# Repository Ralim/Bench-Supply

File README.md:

# Bench-Supply
Small Bench Power Supply files, creating a 48V bench power supply.
This will most likely just contain all the board files used.

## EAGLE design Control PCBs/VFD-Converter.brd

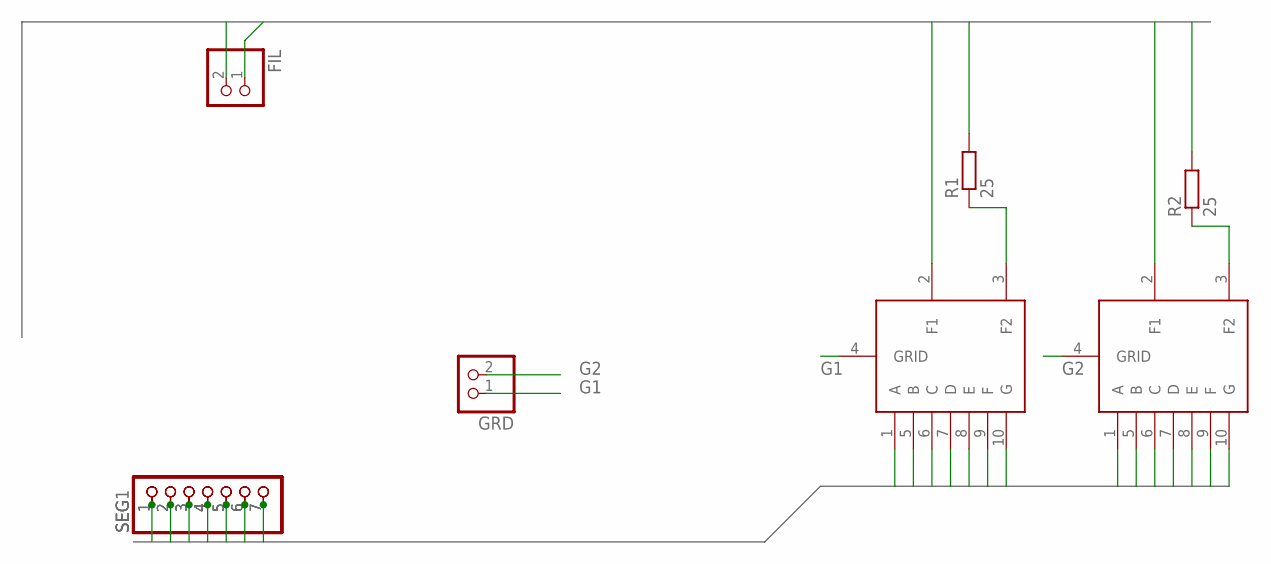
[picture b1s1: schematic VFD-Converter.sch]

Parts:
FIL: PINHD-1X2; 1X02
GRD: PINHD-1X2; 1X02
R1, R2: 25; M0805
SEG, SEG1: PINHD-1X7; 1X07
U$5, U$6: IV-12; NIXIE-11

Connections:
F1: FIL.1, U$5.2 (F1), U$6.2 (F1)
F2: FIL.2, R1.2, R2.2
G1: GRD.1, U$5.4 (GRID)
G2: GRD.2, U$6.4 (GRID)
unnamed: R2.1, U$6.3 (F2)
unnamed: R1.1, U$5.3 (F2)
SEG1: SEG.1, SEG1.1, U$5.1 (A), U$6.1 (A)
SEG2: SEG.2, SEG1.2, U$5.5 (B), U$6.5 (B)
SEG3: SEG.3, SEG1.3, U$5.6 (C), U$6.6 (C)
SEG4: SEG.4, SEG1.4, U$5.7 (D), U$6.7 (D)
SEG5: SEG.5, SEG1.5, U$5.8 (E), U$6.8 (E)
SEG6: SEG.6, SEG1.6, U$5.9 (F), U$6.9 (F)
SEG7: SEG.7, SEG1.7, U$5.10 (G), U$6.10 (G)

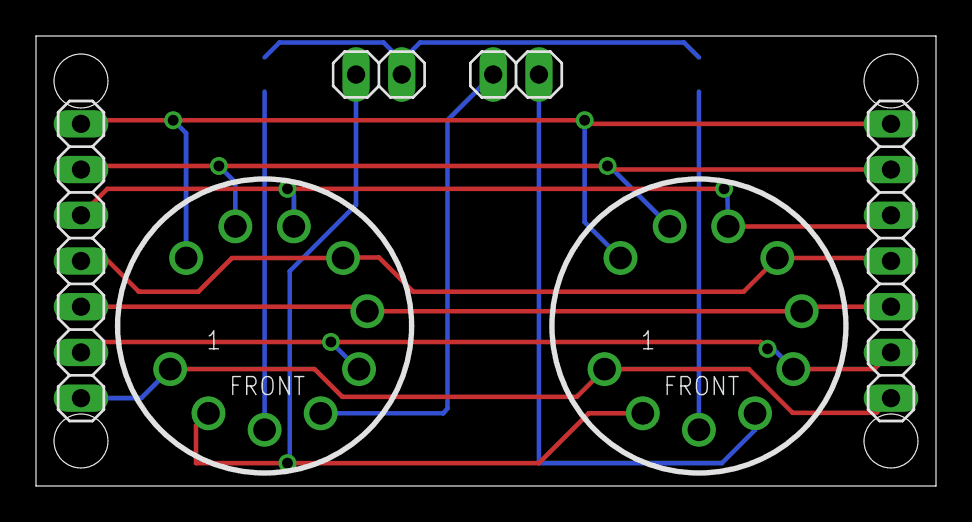
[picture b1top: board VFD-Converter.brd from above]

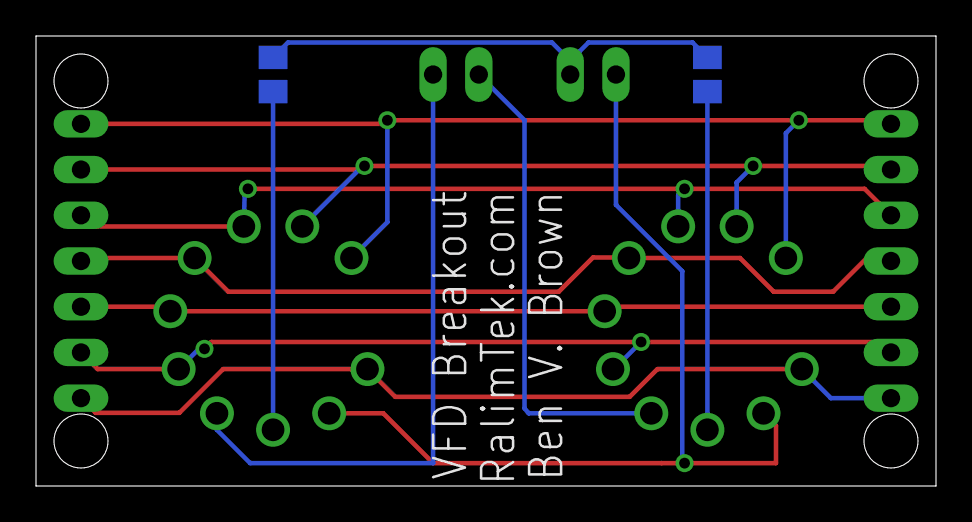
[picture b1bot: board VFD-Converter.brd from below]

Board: 2 copper layers, 50.0 x 25.0 mm, 8 parts (2 on the bottom side), 13 nets.

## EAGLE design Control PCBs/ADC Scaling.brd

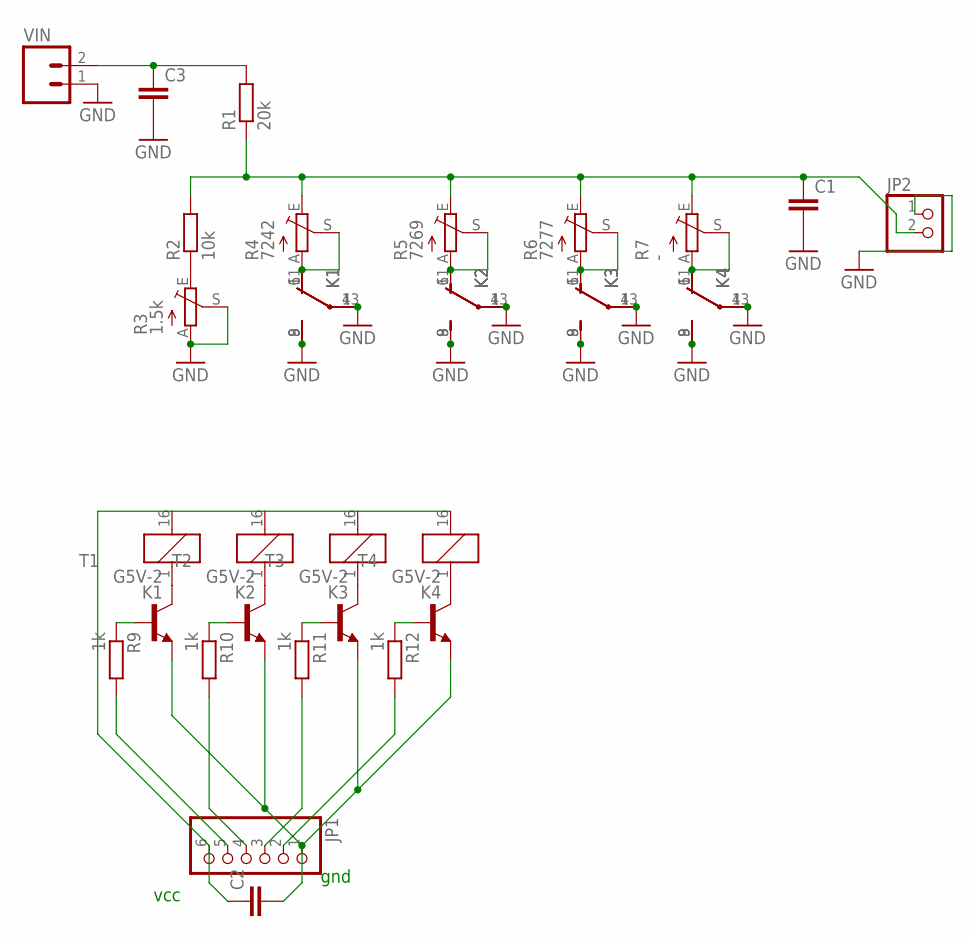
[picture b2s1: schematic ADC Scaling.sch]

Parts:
C1, C2, C3: C-EUC0805; C0805
JP1: PINHD-1X6; 1X06
JP2: PINHD-1X2; 1X02
K1, K2, K3, K4: G5V-2
R1: 20k; M0805
R2: 10k; M0805
R3: 1.5k; RJ9W
R4: 7242; RJ9W
R5: 7269; RJ9W
R6: 7277; RJ9W
R7: -; RJ9W
R9, R10, R11, R12: 1k; M0805
T1, T2, T3, T4: MMBTA42LT1-NPN-SOT23-BEC; SOT23-BEC
VIN: M02POLAR; MOLEX-1X2

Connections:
GND: C1.2, C3.2, JP2.1, K1.4, K1.8 (S), K1.9 (S), K1.13, K2.4, K2.8 (S), K2.9 (S), K2.13, K3.4, K3.8 (S), K3.9 (S), K3.13, K4.4, K4.8 (S), K4.9 (S), K4.13, R3.A, R3.S, VIN.1
GND2: C2.2, JP1.1, T1.E, T2.E, T3.E, T4.E
unnamed: R2.1, R3.E
unnamed: C3.1, R1.2, VIN.2
unnamed: K1.1, T1.C
unnamed: K2.1, T2.C
unnamed: K2.6 (O), K2.11 (O), R5.A, R5.S
unnamed: K1.6 (O), K1.11 (O), R4.A, R4.S
unnamed: K3.1, T3.C
unnamed: K4.1, T4.C
unnamed: R12.1, T4.B
unnamed: R11.1, T3.B
unnamed: R10.1, T2.B
unnamed: R9.1, T1.B
unnamed: K3.6 (O), K3.11 (O), R6.A, R6.S
unnamed: C2.1, JP1.6, K1.16 (2), K2.16 (2), K3.16 (2), K4.16 (2)
unnamed: K4.6 (O), K4.11 (O), R7.A, R7.S
unnamed: C1.1, JP2.2, R1.1, R2.2, R4.E, R5.E, R6.E, R7.E
unnamed: JP1.5, R9.2
unnamed: JP1.4, R10.2
unnamed: JP1.3, R11.2
unnamed: JP1.2, R12.2

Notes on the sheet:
gnd
vcc

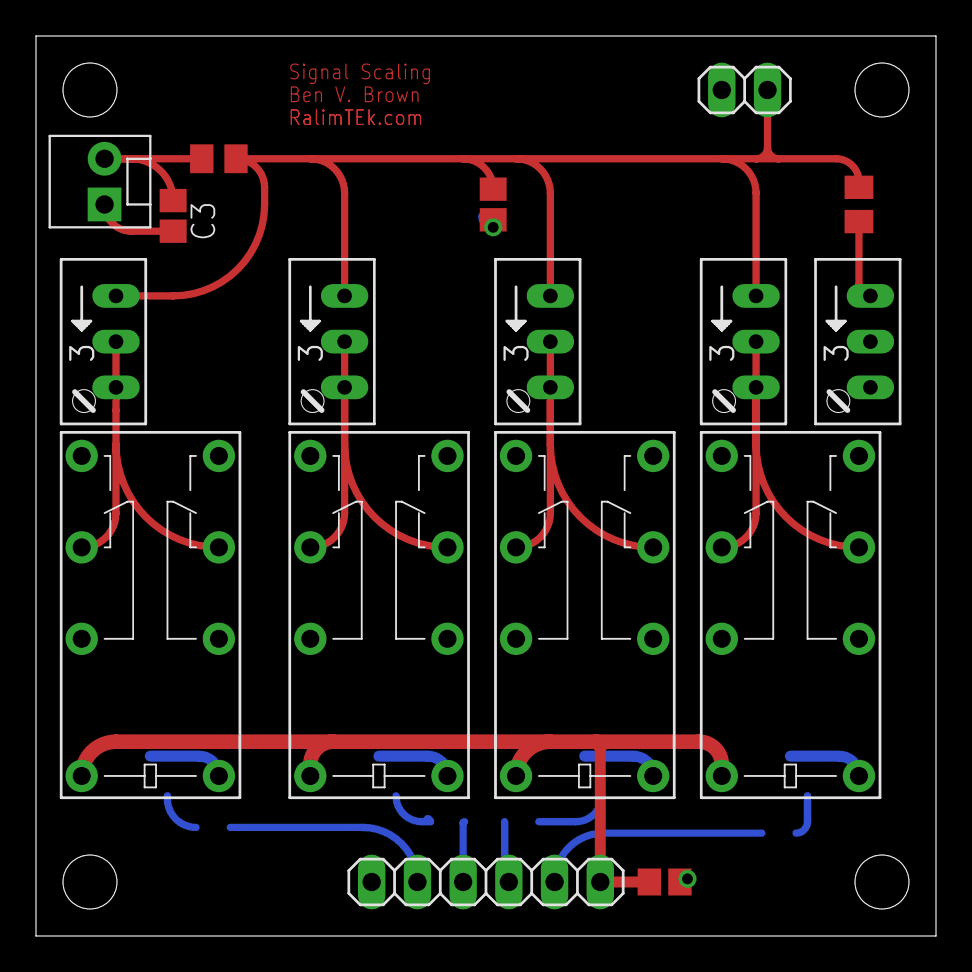
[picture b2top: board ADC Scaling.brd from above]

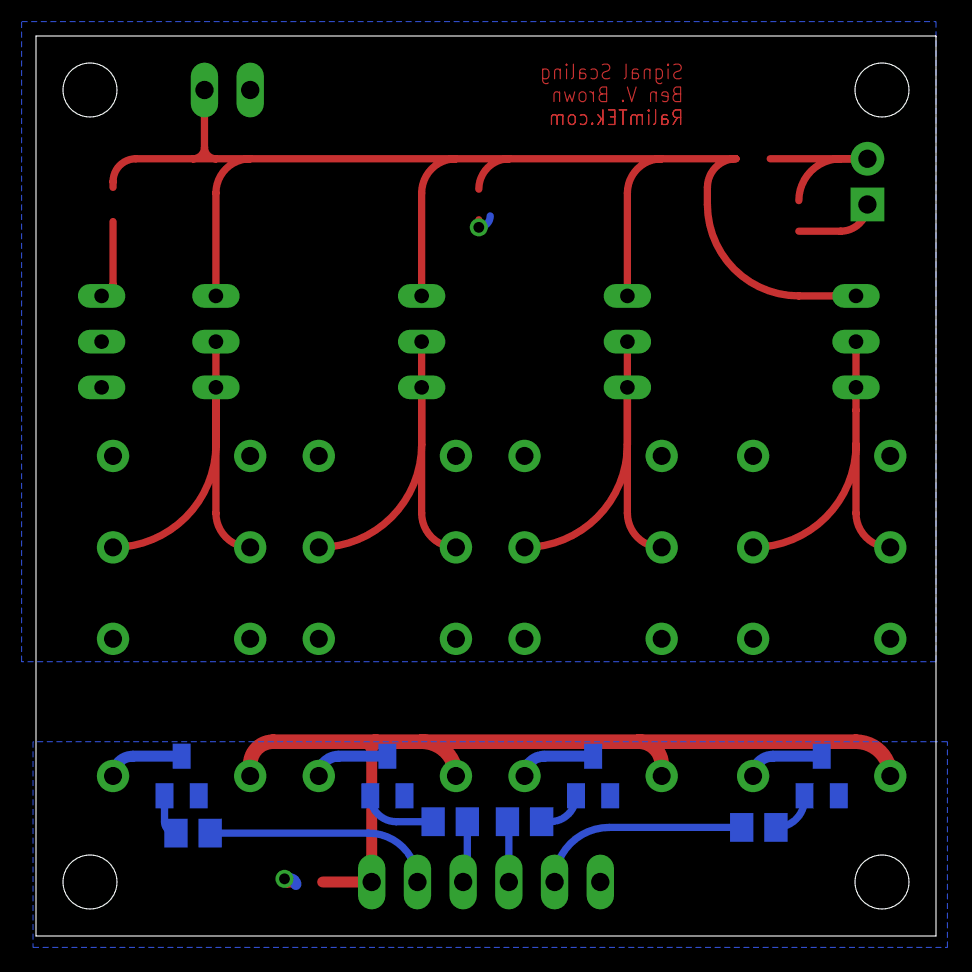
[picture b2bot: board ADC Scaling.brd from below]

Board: 2 copper layers, 50.0 x 50.0 mm, 25 parts (8 on the bottom side), 22 nets.

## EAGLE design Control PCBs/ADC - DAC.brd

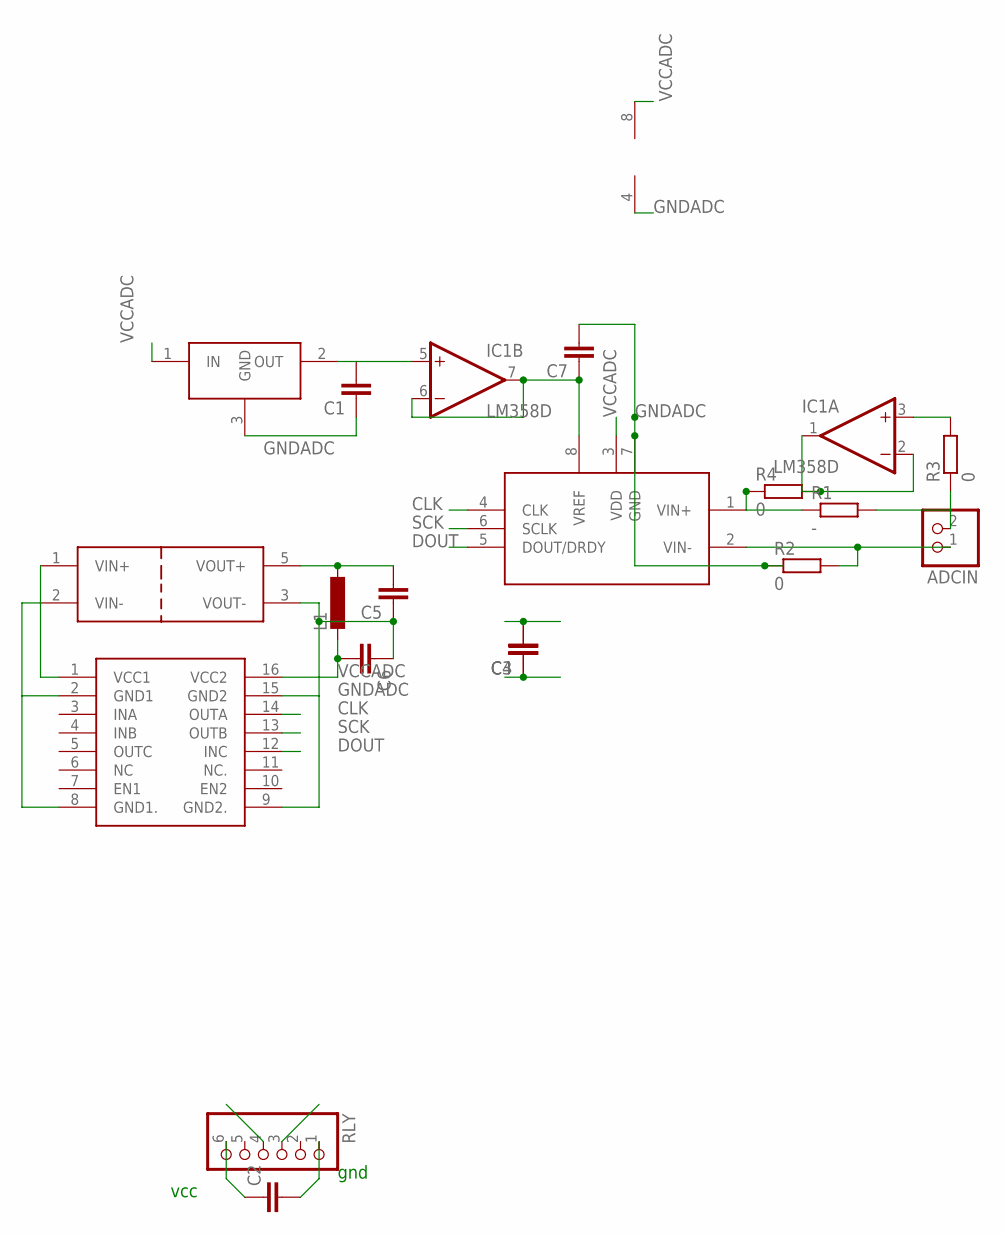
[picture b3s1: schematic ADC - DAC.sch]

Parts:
ADCIN: PINHD-1X2; 1X02
C1, C2, C3, C4, C5, C6, C7: C-EUC0805; C0805
IC1: LM358D; SO08
L1: L-EUL2012C; L2012C
R1: -; M0805
R2, R3, R4: 0; M0805
RLY: PINHD-1X6; 1X06
U$1: ADS1251U; SOIC8
U$2: REF31; SOT23
U$3: ISO7631; SOIC16R
U$4: DCH01

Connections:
ADC+: ADCIN.2, R1.2, R3.1
ADC-: ADCIN.1, R2.2, U$1.2 (VIN-)
CLK: U$1.4 (CLK), U$3.14 (OUTA)
DOUT: U$1.5 (DOUT/DRDY), U$3.12 (INC)
GND2: C2.2, RLY.1
GNDADC: C1.1, C3.1, C4.1, C5.1, C6.1, C7.2, IC1.4 (V-), R2.1, U$1.7 (GND), U$2.3 (GND), U$3.9 (GND2.), U$3.15 (GND2), U$4.3 (VOUT-)
unnamed: C2.1, RLY.6
unnamed: C7.1, IC1.6 (-IN), IC1.7 (OUT), U$1.8 (VREF)
unnamed: C1.2, IC1.5 (+IN), U$2.2 (OUT)
unnamed: IC1.1 (OUT), IC1.2 (-IN), R4.2
unnamed: U$3.2 (GND1), U$3.8 (GND1.), U$4.2 (VIN-)
unnamed: U$3.1 (VCC1), U$4.1 (VIN+)
unnamed: C5.2, L1.1, U$4.5 (VOUT+)
unnamed: IC1.3 (+IN), R3.2
unnamed: R1.1, R4.1, U$1.1 (VIN+)
SCK: U$1.6 (SCLK), U$3.13 (OUTB)
VCCADC: C3.2, C4.2, C6.2, IC1.8 (V+), L1.2, U$1.3 (VDD), U$2.1 (IN), U$3.16 (VCC2)

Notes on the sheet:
gnd
vcc

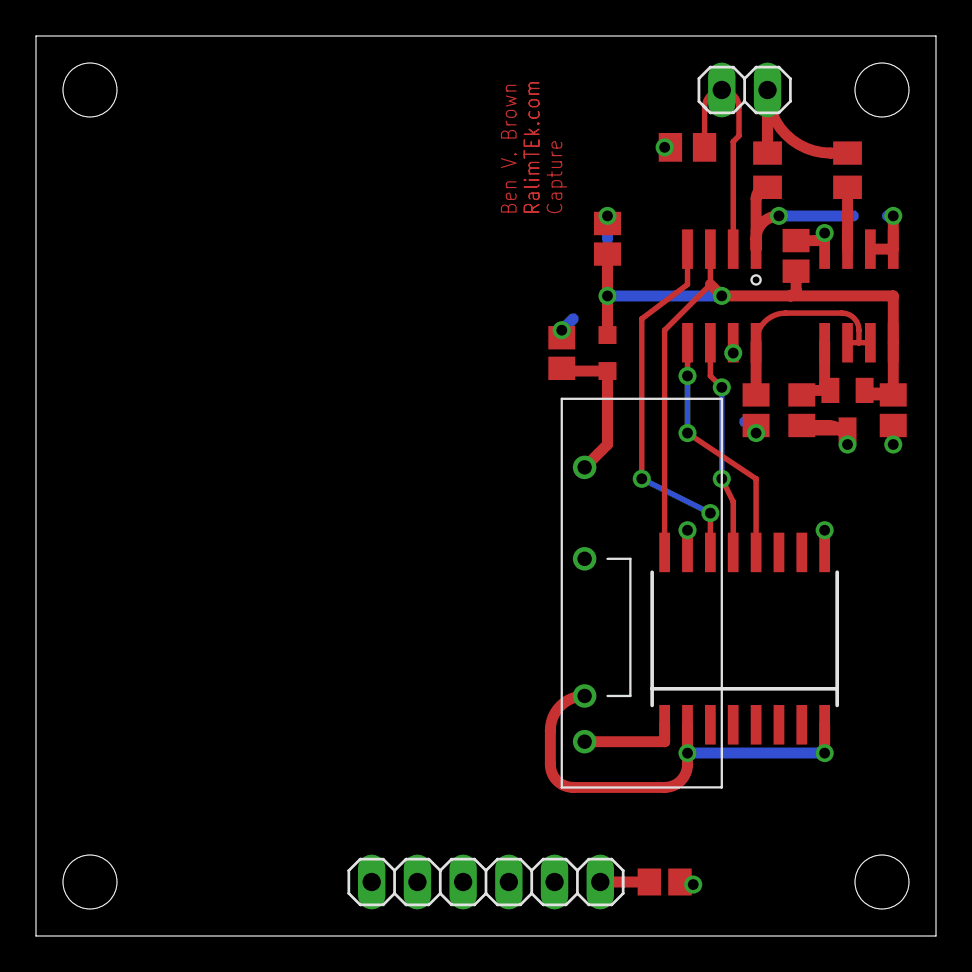
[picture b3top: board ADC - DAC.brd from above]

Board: 2 copper layers, 50.0 x 50.0 mm, 19 parts (1 on the bottom side), 17 nets.

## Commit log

2015-03-12 + Analog Voltage measurement pcb
2015-03-12 +Flip out connector on scaling pcb to aid in routing the adc +Routed ADC part of ADC/DAC board
2015-03-18 +VFD converter
